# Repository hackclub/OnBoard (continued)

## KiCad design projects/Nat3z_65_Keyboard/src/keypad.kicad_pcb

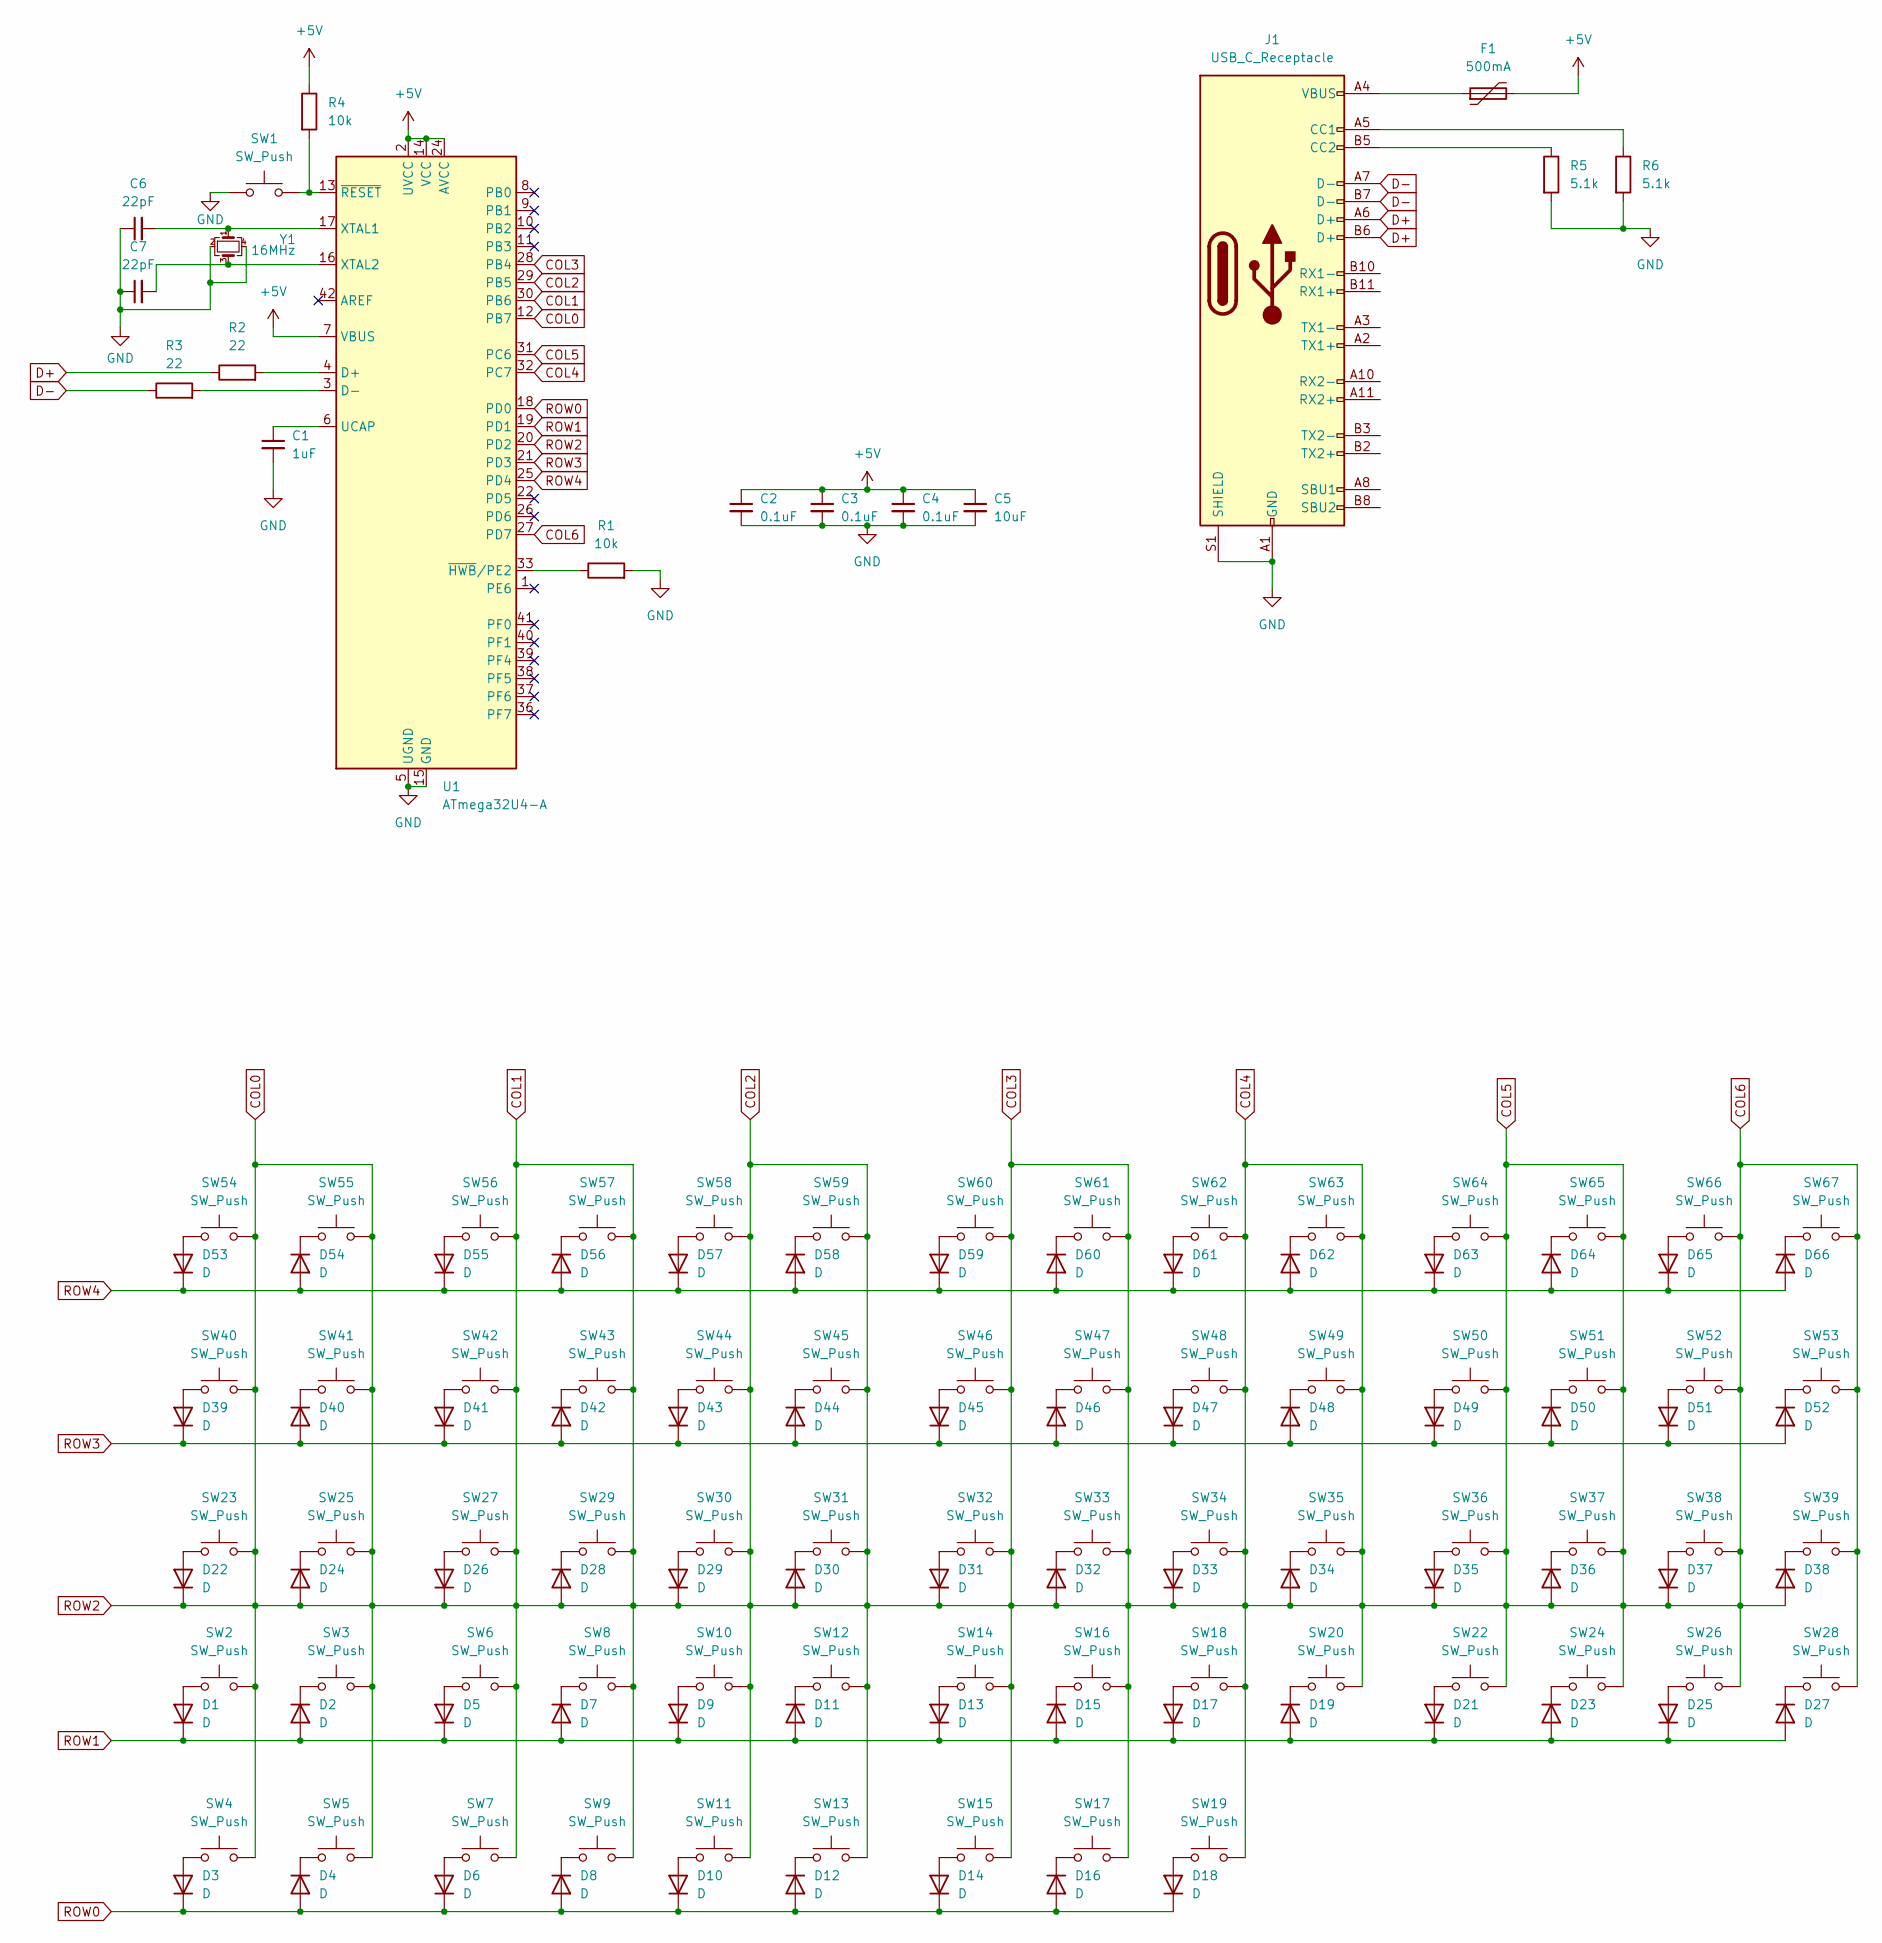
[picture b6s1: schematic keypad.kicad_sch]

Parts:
C1: 1uF; C_0805_2012Metric
C2, C3, C4: 0.1uF; C_0805_2012Metric
C5: 10uF; C_0805_2012Metric
C6, C7: 22pF; C_0805_2012Metric
D1, D2, D3, D4, D5, D6, D7, D8, D9, D10, D11, D12, D13, D14, D15, D16, D17, D18, D19, D21, D22, D23, D24, D25, D26, D27, D28, D29, D30, D31, D32, D33, D34, D35, D36, D37, D38, D39, D40, D41, D42, D43, D44, D45, D46, D47, D48, D49, D50, D51, D52, D53, D54, D55, D56, D57, D58, D59, D60, D61, D62, D63, D64, D65, D66: D; D_SOD-123
F1: 500mA; Fuse_1206_3216Metric_Pad1.42x1.75mm_HandSolder
J1: USB_C_Receptacle; USB_C_Receptacle_HRO_TYPE-C-31-M-12
R1, R4: 10k; R_0805_2012Metric
R2, R3: 22; R_0805_2012Metric
R5, R6: 5.1k; R_0805_2012Metric
SW1: SW_Push; SW_SPST_SKQG_WithStem
SW2, SW38: SW_Push; SW_Cherry_MX_2.25u_PCB
SW3, SW6, SW8, SW10, SW12, SW14, SW15, SW16, SW17, SW18, SW19, SW20, SW22, SW25, SW26, SW27, SW28, SW29, SW30, SW31, SW32, SW33, SW34, SW35, SW36, SW37, SW39, SW41, SW42, SW43, SW44, SW45, SW46, SW47, SW48, SW49, SW50, SW51, SW53, SW54, SW55, SW56, SW57, SW58, SW59, SW60, SW61, SW62, SW63, SW64, SW65, SW67: SW_Push; SW_Cherry_MX_1.00u_PCB
SW4, SW5, SW7, SW11, SW13: SW_Push; SW_Cherry_MX_1.25u_PCB
SW9: SW_Push; SW_Cherry_MX_6.25u_PCB
SW23, SW24: SW_Push; SW_Cherry_MX_1.75u_PCB
SW40, SW52: SW_Push; SW_Cherry_MX_1.50u_PCB
SW66: SW_Push; SW_Cherry_MX_2.00u_PCB
U1: ATmega32U4-A; TQFP-44_10x10mm_P0.8mm
Y1: 16MHz; Crystal_SMD_3225-4Pin_3.2x2.5mm

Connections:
D+: J1.A6 (D+), J1.B6 (D+), R2.1
D-: J1.A7 (D-), J1.B7 (D-), R3.1
GND: C1.2, C2.2, C3.2, C4.2, C5.2, C6.1, C7.1, J1.A1 (GND), J1.A12 (GND), J1.B1 (GND), J1.B12 (GND), J1.S1 (SHIELD), R1.2, R5.2, R6.2, SW1.1, U1.5 (UGND), U1.15 (GND), U1.23 (GND), U1.35 (GND), U1.43 (GND), Y1.2, Y1.4; also elsewhere on the board
unnamed: D1.2 (A), SW2.1
unnamed: D2.1 (K), SW3.1
unnamed: D3.2 (A), SW4.1
unnamed: D4.1 (K), SW5.1
unnamed: D5.2 (A), SW6.1
unnamed: D6.2 (A), SW7.1
unnamed: D7.1 (K), SW8.1
unnamed: D8.1 (K), SW9.1
unnamed: D9.2 (A), SW10.1
unnamed: D10.2 (A), SW11.1
unnamed: D11.1 (K), SW12.1
unnamed: D12.1 (K), SW13.1
unnamed: D13.2 (A), SW14.1
unnamed: D14.2 (A), SW15.1
unnamed: D15.1 (K), SW16.1
unnamed: D16.1 (K), SW17.1
unnamed: D17.2 (A), SW18.1
unnamed: D18.2 (A), SW19.1
unnamed: D19.1 (K), SW20.1
unnamed: D21.2 (A), SW22.1
unnamed: D22.2 (A), SW23.1
unnamed: D23.1 (K), SW24.1
unnamed: D24.1 (K), SW25.1
unnamed: D25.2 (A), SW26.1
unnamed: D26.2 (A), SW27.1
unnamed: D27.1 (K), SW28.1
unnamed: D28.1 (K), SW29.1
unnamed: D29.2 (A), SW30.1
unnamed: D30.1 (K), SW31.1
unnamed: D31.2 (A), SW32.1
unnamed: D32.1 (K), SW33.1
unnamed: D33.2 (A), SW34.1
unnamed: D34.1 (K), SW35.1
unnamed: D35.2 (A), SW36.1
unnamed: D36.1 (K), SW37.1
unnamed: D37.2 (A), SW38.1
unnamed: D38.1 (K), SW39.1
unnamed: D39.2 (A), SW40.1
unnamed: D40.1 (K), SW41.1
unnamed: D41.2 (A), SW42.1
unnamed: D42.1 (K), SW43.1
unnamed: D43.2 (A), SW44.1
unnamed: D44.1 (K), SW45.1
unnamed: D45.2 (A), SW46.1
unnamed: D46.1 (K), SW47.1
unnamed: D47.2 (A), SW48.1
unnamed: D48.1 (K), SW49.1
unnamed: D49.2 (A), SW50.1
unnamed: D50.1 (K), SW51.1
unnamed: D51.2 (A), SW52.1
unnamed: D52.1 (K), SW53.1
unnamed: D53.2 (A), SW54.1
unnamed: D54.1 (K), SW55.1
unnamed: D55.2 (A), SW56.1
unnamed: D56.1 (K), SW57.1
unnamed: D57.2 (A), SW58.1
unnamed: D58.1 (K), SW59.1
unnamed: D59.2 (A), SW60.1
unnamed: D60.1 (K), SW61.1
unnamed: D61.2 (A), SW62.1
unnamed: D62.1 (K), SW63.1
unnamed: D63.2 (A), SW64.1
unnamed: D64.1 (K), SW65.1
unnamed: D65.2 (A), SW66.1
unnamed: D66.1 (K), SW67.1
unnamed: J1.A5 (CC1), R6.1
unnamed: J1.B5 (CC2), R5.1
unnamed: R2.2, U1.4 (D+)
unnamed: R3.2, U1.3 (D-)
unnamed: C1.1, U1.6 (UCAP)
unnamed: C6.2, U1.17 (XTAL1), Y1.1
unnamed: C7.2, U1.16 (XTAL2), Y1.3
unnamed: R1.1, U1.33 (~HWB/PE2)
unnamed: R4.2, SW1.2, U1.13 (~RESET)
ROW0: D3.1 (K), D4.2 (A), D6.1 (K), D8.2 (A), D10.1 (K), D12.2 (A), D14.1 (K), D16.2 (A), D18.1 (K), U1.18 (PD0)
ROW1: D1.1 (K), D2.2 (A), D5.1 (K), D7.2 (A), D9.1 (K), D11.2 (A), D13.1 (K), D15.2 (A), D17.1 (K), D19.2 (A), D21.1 (K), D23.2 (A), D25.1 (K), D27.2 (A), U1.19 (PD1)
ROW3: D39.1 (K), D40.2 (A), D41.1 (K), D42.2 (A), D43.1 (K), D44.2 (A), D45.1 (K), D46.2 (A), D47.1 (K), D48.2 (A), D49.1 (K), D50.2 (A), D51.1 (K), D52.2 (A), U1.21 (PD3)
ROW4: D53.1 (K), D54.2 (A), D55.1 (K), D56.2 (A), D57.1 (K), D58.2 (A), D59.1 (K), D60.2 (A), D61.1 (K), D62.2 (A), D63.1 (K), D64.2 (A), D65.1 (K), D66.2 (A), U1.25 (PD4)

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
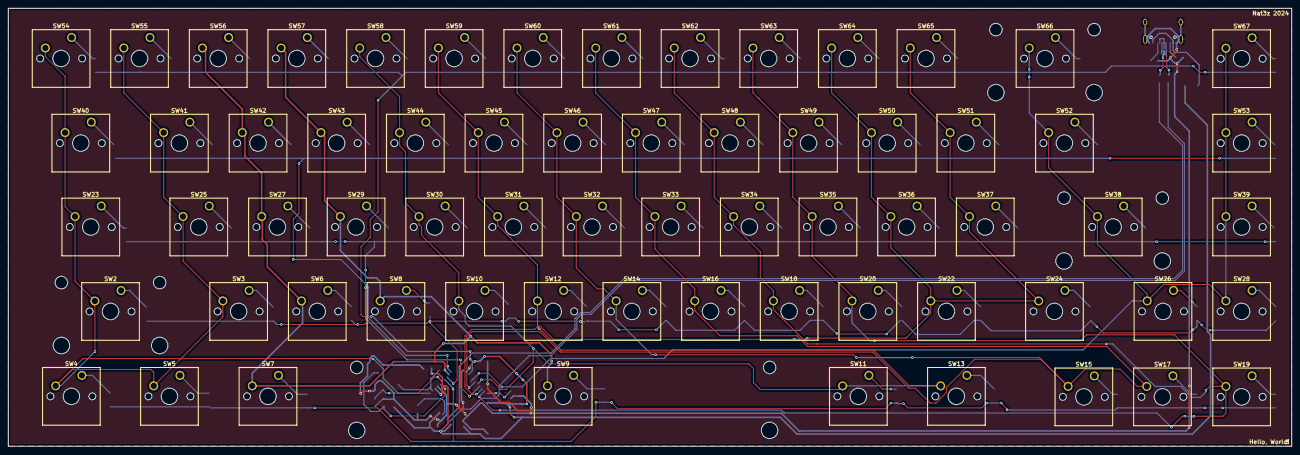
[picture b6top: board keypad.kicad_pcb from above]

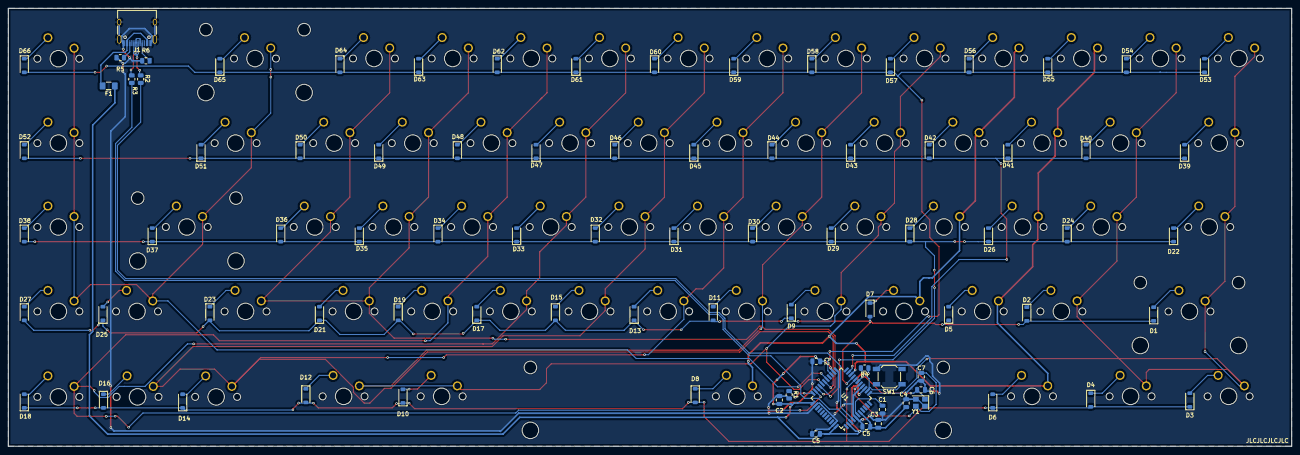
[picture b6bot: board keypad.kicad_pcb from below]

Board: 2 copper layers, 310.8 x 106.1 mm, 150 parts (85 on the bottom side), 91 nets.

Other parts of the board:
C2#2: 0.1uF; C_0805_2012Metric
C5#2: 10uF; C_0805_2012Metric

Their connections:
GND: C2#2.2, C5#2.2; also elsewhere on the board

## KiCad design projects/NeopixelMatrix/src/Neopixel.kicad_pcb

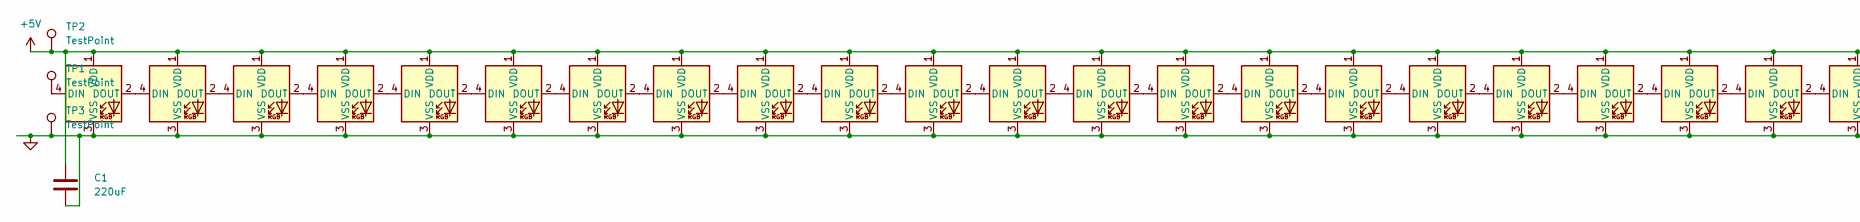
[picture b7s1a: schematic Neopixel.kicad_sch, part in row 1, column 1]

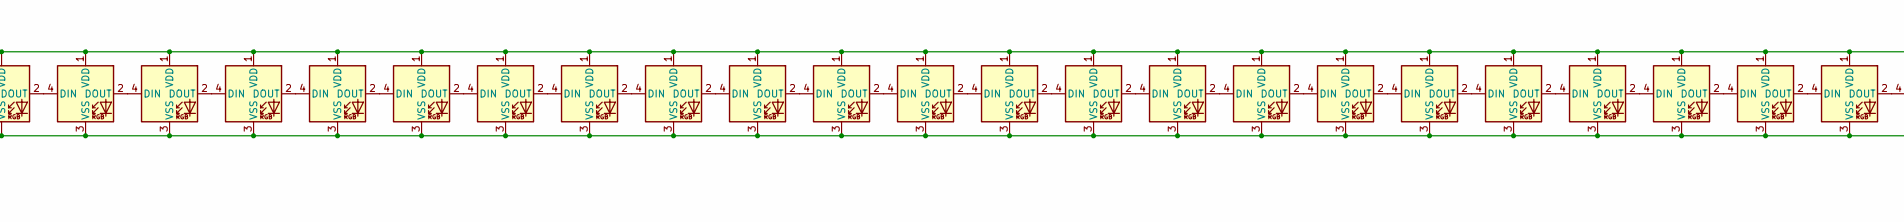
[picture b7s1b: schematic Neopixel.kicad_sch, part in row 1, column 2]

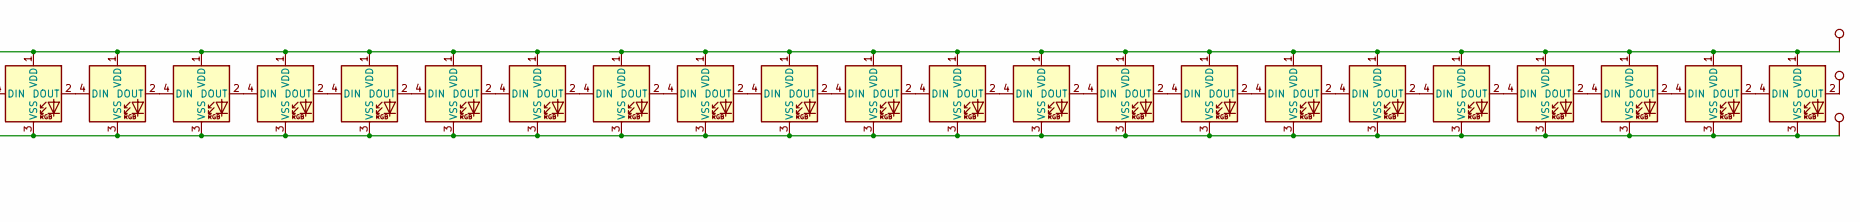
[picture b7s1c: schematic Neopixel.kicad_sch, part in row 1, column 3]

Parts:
C1: 220uF; C_1206_3216Metric; LCSC C412252
D1, D2, D3, D4, D5, D6, D7, D8, D9, D10, D11, D12, D13, D14, D15, D16, D17, D18, D19, D20, D21, D22, D23, D24, D25, D26, D27, D28, D29, D30, D31, D32, D33, D34, D35, D36, D37, D38, D39, D40, D41, D42, D43, D44, D45, D46, D47, D48, D49, D50, D51, D52, D53, D54, D55, D56, D57, D58, D59, D60, D61, D62, D63, D64: WS2812B; LED_WS2812B_PLCC4_5.0x5.0mm_P3.2mm
TP1, TP2, TP3, TP4, TP5, TP6: TestPoint

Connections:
+5V: C1.1, D1.1 (VDD), D2.1 (VDD), D3.1 (VDD), D4.1 (VDD), D5.1 (VDD), D6.1 (VDD), D7.1 (VDD), D8.1 (VDD), D9.1 (VDD), D10.1 (VDD), D11.1 (VDD), D12.1 (VDD), D13.1 (VDD), D14.1 (VDD), D15.1 (VDD), D16.1 (VDD), D17.1 (VDD), D18.1 (VDD), D19.1 (VDD), D20.1 (VDD), D21.1 (VDD), D22.1 (VDD), D23.1 (VDD), D24.1 (VDD), D25.1 (VDD), D26.1 (VDD), D27.1 (VDD), D28.1 (VDD), D29.1 (VDD), D30.1 (VDD), D31.1 (VDD), D32.1 (VDD), D33.1 (VDD), D34.1 (VDD), D35.1 (VDD), D36.1 (VDD), D37.1 (VDD), D38.1 (VDD), D39.1 (VDD), D40.1 (VDD), D41.1 (VDD), D42.1 (VDD), D43.1 (VDD), D44.1 (VDD), D45.1 (VDD), D46.1 (VDD), D47.1 (VDD), D48.1 (VDD), D49.1 (VDD), D50.1 (VDD), D51.1 (VDD), D52.1 (VDD), D53.1 (VDD), D54.1 (VDD), D55.1 (VDD), D56.1 (VDD), D57.1 (VDD), D58.1 (VDD), D59.1 (VDD), D60.1 (VDD), D61.1 (VDD), D62.1 (VDD), D63.1 (VDD), D64.1 (VDD), TP2.1, TP5.1; also elsewhere on the board
GND: C1.2, D1.3 (VSS), D2.3 (VSS), D3.3 (VSS), D4.3 (VSS), D5.3 (VSS), D6.3 (VSS), D7.3 (VSS), D8.3 (VSS), D9.3 (VSS), D10.3 (VSS), D11.3 (VSS), D12.3 (VSS), D13.3 (VSS), D14.3 (VSS), D15.3 (VSS), D16.3 (VSS), D17.3 (VSS), D18.3 (VSS), D19.3 (VSS), D20.3 (VSS), D21.3 (VSS), D22.3 (VSS), D23.3 (VSS), D24.3 (VSS), D25.3 (VSS), D26.3 (VSS), D27.3 (VSS), D28.3 (VSS), D29.3 (VSS), D30.3 (VSS), D31.3 (VSS), D32.3 (VSS), D33.3 (VSS), D34.3 (VSS), D35.3 (VSS), D36.3 (VSS), D37.3 (VSS), D38.3 (VSS), D39.3 (VSS), D40.3 (VSS), D41.3 (VSS), D42.3 (VSS), D43.3 (VSS), D44.3 (VSS), D45.3 (VSS), D46.3 (VSS), D47.3 (VSS), D48.3 (VSS), D49.3 (VSS), D50.3 (VSS), D51.3 (VSS), D52.3 (VSS), D53.3 (VSS), D54.3 (VSS), D55.3 (VSS), D56.3 (VSS), D57.3 (VSS), D58.3 (VSS), D59.3 (VSS), D60.3 (VSS), D61.3 (VSS), D62.3 (VSS), D63.3 (VSS), D64.3 (VSS), TP3.1, TP4.1; also elsewhere on the board
unnamed 2: D1.4 (DIN), TP1.1; also elsewhere on the board
unnamed: D1.2 (DOUT), D2.4 (DIN)
unnamed: D2.2 (DOUT), D3.4 (DIN)
unnamed: D3.2 (DOUT), D4.4 (DIN)
unnamed: D4.2 (DOUT), D5.4 (DIN)
unnamed: D5.2 (DOUT), D6.4 (DIN)
unnamed: D6.2 (DOUT), D7.4 (DIN)
unnamed: D7.2 (DOUT), D8.4 (DIN)
unnamed: D8.2 (DOUT), D9.4 (DIN)
unnamed: D9.2 (DOUT), D10.4 (DIN)
unnamed: D10.2 (DOUT), D11.4 (DIN)
unnamed: D11.2 (DOUT), D12.4 (DIN)
unnamed: D12.2 (DOUT), D13.4 (DIN)
unnamed: D13.2 (DOUT), D14.4 (DIN)
unnamed: D14.2 (DOUT), D15.4 (DIN)
unnamed: D15.2 (DOUT), D16.4 (DIN)
unnamed: D16.2 (DOUT), D17.4 (DIN)
unnamed: D17.2 (DOUT), D18.4 (DIN)
unnamed: D18.2 (DOUT), D19.4 (DIN)
unnamed: D19.2 (DOUT), D20.4 (DIN)
unnamed: D20.2 (DOUT), D21.4 (DIN)
unnamed: D21.2 (DOUT), D22.4 (DIN)
unnamed: D22.2 (DOUT), D23.4 (DIN)
unnamed: D23.2 (DOUT), D24.4 (DIN)
unnamed: D24.2 (DOUT), D25.4 (DIN)
unnamed: D25.2 (DOUT), D26.4 (DIN)
unnamed: D26.2 (DOUT), D27.4 (DIN)
unnamed: D27.2 (DOUT), D28.4 (DIN)
unnamed: D28.2 (DOUT), D29.4 (DIN)
unnamed: D29.2 (DOUT), D30.4 (DIN)
unnamed: D30.2 (DOUT), D31.4 (DIN)
unnamed: D31.2 (DOUT), D32.4 (DIN)
unnamed: D32.2 (DOUT), D33.4 (DIN)
unnamed: D33.2 (DOUT), D34.4 (DIN)
unnamed: D34.2 (DOUT), D35.4 (DIN)
unnamed: D35.2 (DOUT), D36.4 (DIN)
unnamed: D36.2 (DOUT), D37.4 (DIN)
unnamed: D37.2 (DOUT), D38.4 (DIN)
unnamed: D38.2 (DOUT), D39.4 (DIN)
unnamed: D39.2 (DOUT), D40.4 (DIN)
unnamed: D40.2 (DOUT), D41.4 (DIN)
unnamed: D41.2 (DOUT), D42.4 (DIN)
unnamed: D42.2 (DOUT), D43.4 (DIN)
unnamed: D43.2 (DOUT), D44.4 (DIN)
unnamed: D44.2 (DOUT), D45.4 (DIN)
unnamed: D45.2 (DOUT), D46.4 (DIN)
unnamed: D46.2 (DOUT), D47.4 (DIN)
unnamed: D47.2 (DOUT), D48.4 (DIN)
unnamed: D48.2 (DOUT), D49.4 (DIN)
unnamed: D49.2 (DOUT), D50.4 (DIN)
unnamed: D50.2 (DOUT), D51.4 (DIN)
unnamed: D51.2 (DOUT), D52.4 (DIN)
unnamed: D52.2 (DOUT), D53.4 (DIN)
unnamed: D53.2 (DOUT), D54.4 (DIN)
unnamed: D54.2 (DOUT), D55.4 (DIN)
unnamed: D55.2 (DOUT), D56.4 (DIN)
unnamed: D56.2 (DOUT), D57.4 (DIN)
unnamed: D57.2 (DOUT), D58.4 (DIN)
unnamed: D58.2 (DOUT), D59.4 (DIN)
unnamed: D59.2 (DOUT), D60.4 (DIN)
unnamed: D60.2 (DOUT), D61.4 (DIN)
unnamed: D61.2 (DOUT), D62.4 (DIN)
unnamed: D62.2 (DOUT), D63.4 (DIN)
unnamed: D63.2 (DOUT), D64.4 (DIN)
unnamed 66: D64.2 (DOUT), TP6.1; also elsewhere on the board

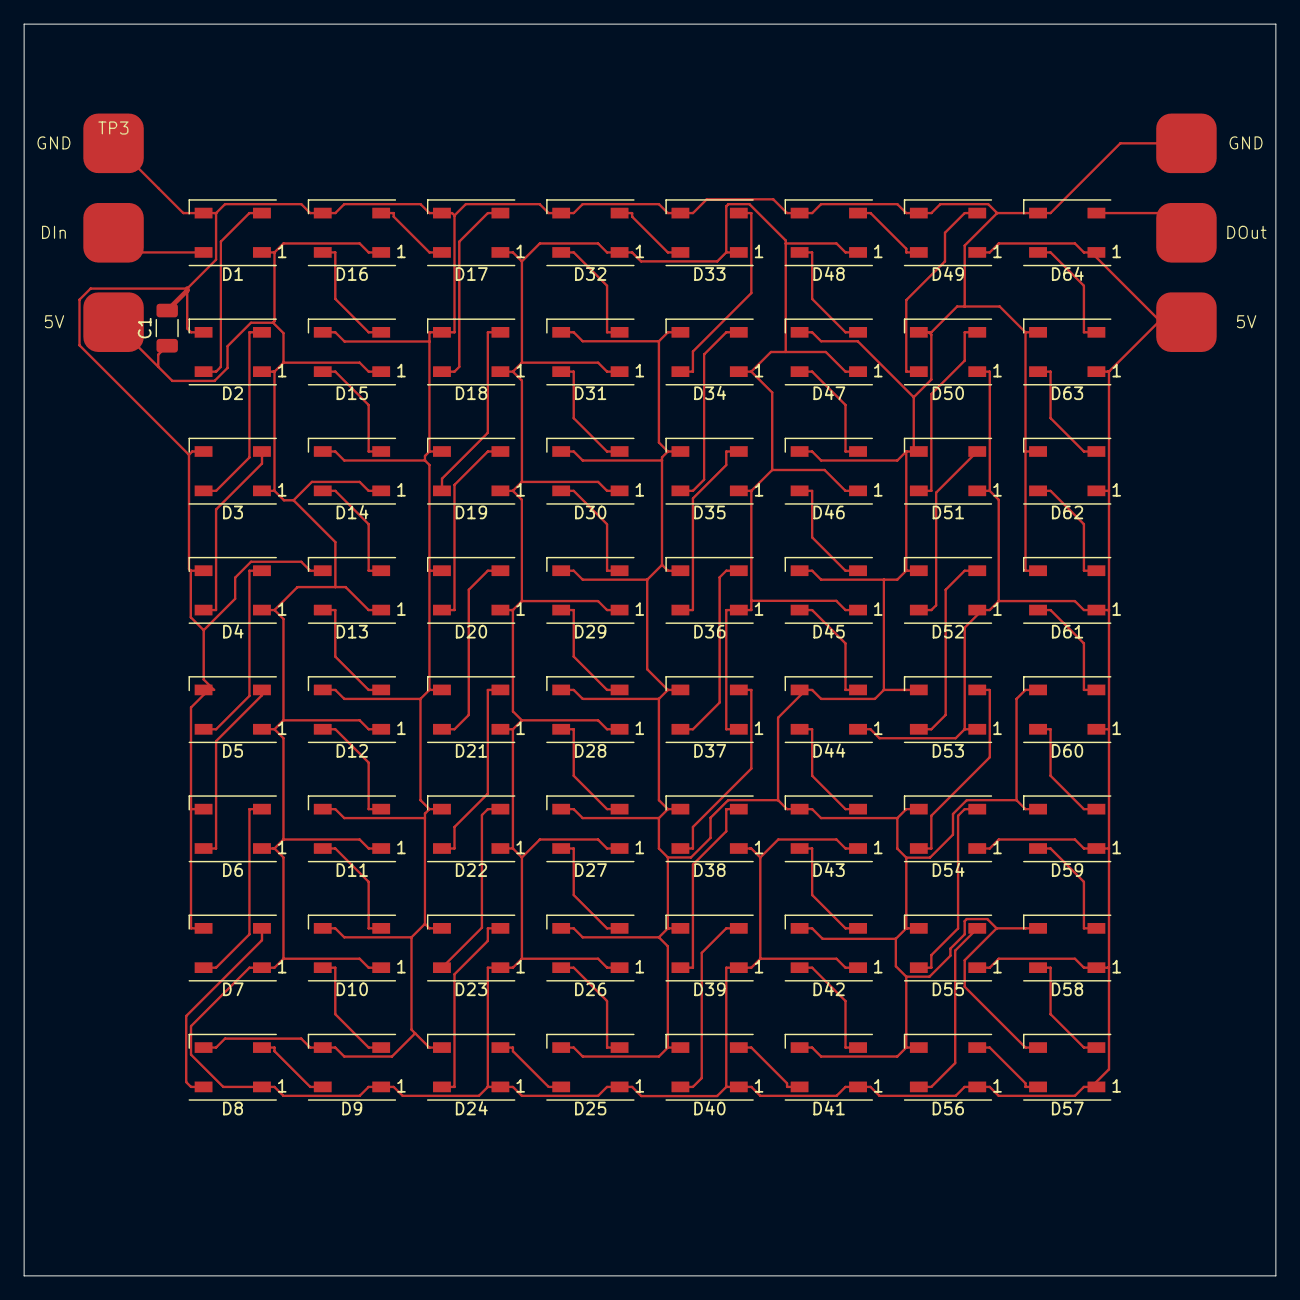
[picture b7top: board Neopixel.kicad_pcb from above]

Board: 2 copper layers, 105.0 x 105.0 mm, 71 parts (0 on the bottom side), 67 nets.

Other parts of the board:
5V, 5V#2: TestPoint
DIn: TestPoint
DOut: TestPoint
GND: TestPoint

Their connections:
+5V: 5V.1, 5V#2.1; also elsewhere on the board
GND: GND.1; also elsewhere on the board
unnamed 2: DIn.1; also elsewhere on the board
unnamed 66: DOut.1; also elsewhere on the board
